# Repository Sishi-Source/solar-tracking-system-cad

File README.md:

# Solar Tracking System [nickos]

## Getting started

To make it easy for you to get started with GitLab, here's a list of recommended next steps.

Already a pro? Just edit this README.md and make it your own. Want to make it easy? [Use the template at the bottom](#editing-this-readme)!

## Add your files

- [ ] [Create](https://docs.gitlab.com/ee/user/project/repository/web_editor.html#create-a-file) or [upload](https://docs.gitlab.com/ee/user/project/repository/web_editor.html#upload-a-file) files
- [ ] [Add files using the command line](https://docs.gitlab.com/topics/git/add_files/#add-files-to-a-git-repository) or push an existing Git repository with the following command:

```
cd existing_repo
git remote add origin https://gitlab.com/Sishi-Source/solar-tracking-system.git
git branch -M main
git push -uf origin main
```

## Integrate with your tools

- [ ] [Set up project integrations](https://gitlab.com/Sishi-Source/solar-tracking-system/-/settings/integrations)

## Collaborate with your team

- [ ] [Invite team members and collaborators](https://docs.gitlab.com/ee/user/project/members/)
- [ ] [Create a new merge request](https://docs.gitlab.com/ee/user/project/merge_requests/creating_merge_requests.html)
- [ ] [Automatically close issues from merge requests](https://docs.gitlab.com/ee/user/project/issues/managing_issues.html#closing-issues-automatically)
- [ ] [Enable merge request approvals](https://docs.gitlab.com/ee/user/project/merge_requests/approvals/)
- [ ] [Set auto-merge](https://docs.gitlab.com/user/project/merge_requests/auto_merge/)

## Test and Deploy

Use the built-in continuous integration in GitLab.

- [ ] [Get started with GitLab CI/CD](https://docs.gitlab.com/ee/ci/quick_start/)
- [ ] [Analyze your code for known vulnerabilities with Static Application Security Testing (SAST)](https://docs.gitlab.com/ee/user/application_security/sast/)
- [ ] [Deploy to Kubernetes, Amazon EC2, or Amazon ECS using Auto Deploy](https://docs.gitlab.com/ee/topics/autodevops/requirements.html)
- [ ] [Use pull-based deployments for improved Kubernetes management](https://docs.gitlab.com/ee/user/clusters/agent/)
- [ ] [Set up protected environments](https://docs.gitlab.com/ee/ci/environments/protected_environments.html)

***

# Editing this README

When you're ready to make this README your own, just edit this file and use the handy template below (or feel free to structure it however you want - this is just a starting point!). Thanks to [makeareadme.com](https://www.makeareadme.com/) for this template.

## Suggestions for a good README

Every project is different, so consider which of these sections apply to yours. The sections used in the template are suggestions for most open source projects. Also keep in mind that while a README can be too long and detailed, too long is better than too short. If you think your README is too long, consider utilizing another form of documentation rather than cutting out information.

## Name
Choose a self-explaining name for your project.

## Description
Let people know what your project can do specifically. Provide context and add a link to any reference visitors might be unfamiliar with. A list of Features or a Background subsection can also be added here. If there are alternatives to your project, this is a good place to list differentiating factors.

## Badges
On some READMEs, you may see small images that convey metadata, such as whether or not all the tests are passing for the project. You can use Shields to add some to your README. Many services also have instructions for adding a badge.

## Visuals
Depending on what you are making, it can be a good idea to include screenshots or even a video (you'll frequently see GIFs rather than actual videos). Tools like ttygif can help, but check out Asciinema for a more sophisticated method.

## Installation
Within a particular ecosystem, there may be a common way of installing things, such as using Yarn, NuGet, or Homebrew. However, consider the possibility that whoever is reading your README is a novice and would like more guidance. Listing specific steps helps remove ambiguity and gets people to using your project as quickly as possible. If it only runs in a specific context like a particular programming language version or operating system or has dependencies that have to be installed manually, also add a Requirements subsection.

## Usage
Use examples liberally, and show the expected output if you can. It's helpful to have inline the smallest example of usage that you can demonstrate, while providing links to more sophisticated examples if they are too long to reasonably include in the README.

## Support
Tell people where they can go to for help. It can be any combination of an issue tracker, a chat room, an email address, etc.

## Roadmap
If you have ideas for releases in the future, it is a good idea to list them in the README.

## Contributing
State if you are open to contributions and what your requirements are for accepting them.

For people who want to make changes to your project, it's helpful to have some documentation on how to get started. Perhaps there is a script that they should run or some environment variables that they need to set. Make these steps explicit. These instructions could also be useful to your future self.

You can also document commands to lint the code or run tests. These steps help to ensure high code quality and reduce the likelihood that the changes inadvertently break something. Having instructions for running tests is especially helpful if it requires external setup, such as starting a Selenium server for testing in a browser.

## Authors and acknowledgment
Show your appreciation to those who have contributed to the project.

## License
For open source projects, say how it is licensed.

## Project status
If you have run out of energy or time for your project, put a note at the top of the README saying that development has slowed down or stopped completely. Someone may choose to fork your project or volunteer to step in as a maintainer or owner, allowing your project to keep going. You can also make an explicit request for maintainers.

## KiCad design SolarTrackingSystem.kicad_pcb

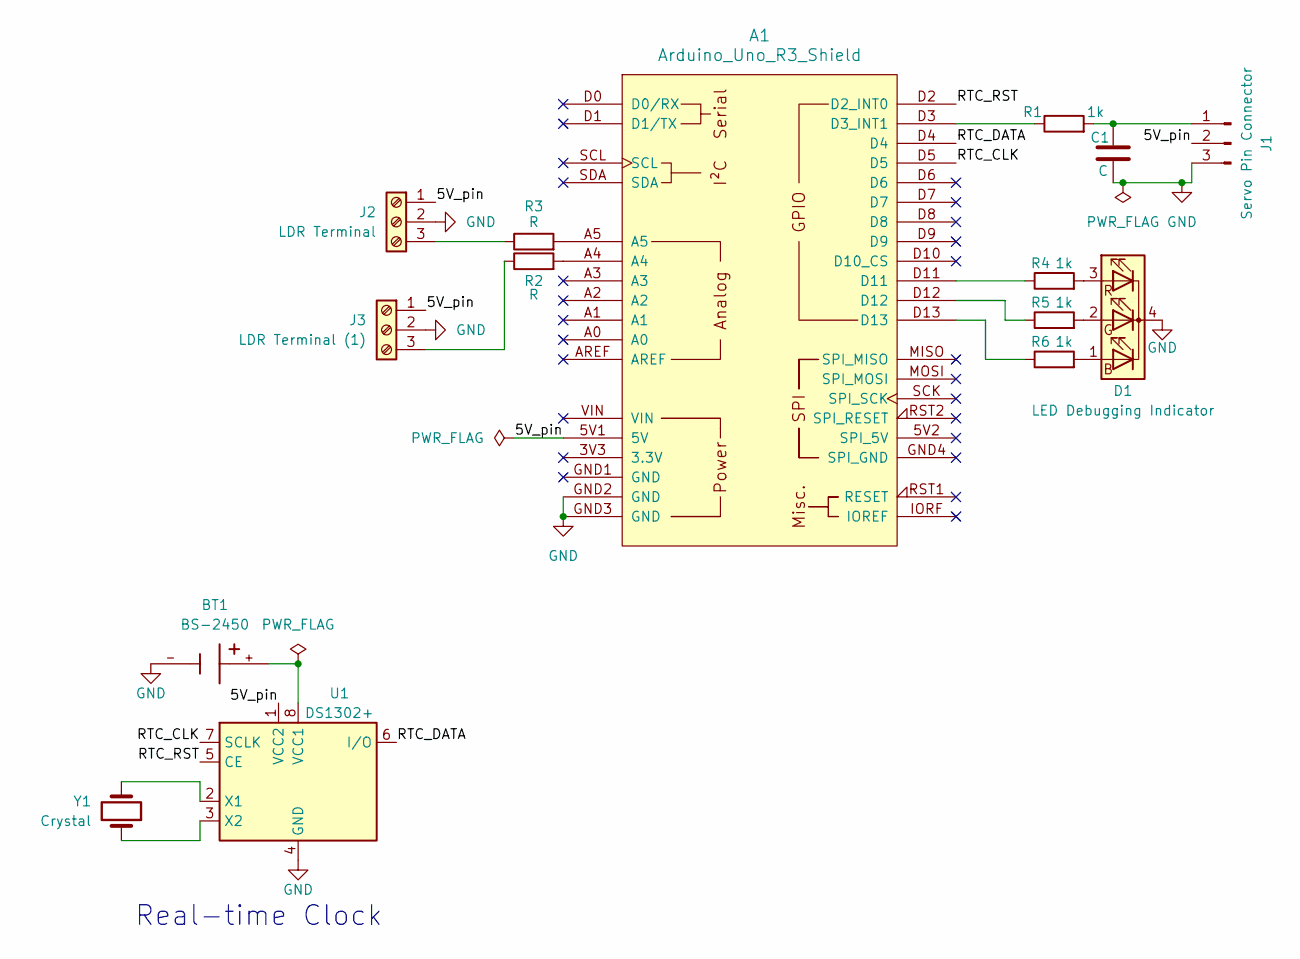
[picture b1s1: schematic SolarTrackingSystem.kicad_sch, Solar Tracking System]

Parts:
A1: Arduino_Uno_R3_Shield
BT1: BS-2450; BAT_BS-2450
C1: C; C_Radial_D5.0mm_H7.0mm_P2.00mm
D1: LED Debugging Indicator; LED_D5.0mm-4_RGB
J1: Servo Pin Connector; PinHeader_1x03_P2.54mm_Vertical
J2: LDR Terminal; TerminalBlock_Phoenix_MKDS-1,5-3_1x03_P5.00mm_Horizontal
J3: LDR Terminal (1); TerminalBlock_Phoenix_MKDS-1,5-3_1x03_P5.00mm_Horizontal
R1, R4, R5, R6: 1k; R_Axial_DIN0207_L6.3mm_D2.5mm_P7.62mm_Horizontal
R2, R3: R; R_Axial_DIN0207_L6.3mm_D2.5mm_P7.62mm_Horizontal
U1: DS1302+; DIP-8_W7.62mm
Y1: Crystal; Crystal_DS10_D1.0mm_L4.3mm_Horizontal

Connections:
/5V_pin: A1.5V1 (5V), J1.2, J2.1, J3.1, U1.1 (VCC2)
/RTC_CLK: A1.D5, U1.7 (SCLK)
/RTC_DATA: A1.D4, U1.6 (I/O)
/RTC_RST: A1.D2 (D2_INT0), U1.5 (CE)
GND: A1.GND2 (GND), A1.GND3 (GND), BT1.-, C1.2, D1.4 (K), J1.3, J2.2, J3.2, U1.4 (GND)
unnamed: A1.D3 (D3_INT1), R1.1
unnamed: A1.A4, R2.2
unnamed: A1.A5, R3.2
unnamed: A1.D11, R4.1
unnamed: A1.D12, R5.1
unnamed: A1.D13, R6.1
unnamed: D1.1 (BA), R6.2
unnamed: D1.2 (GA), R5.2
unnamed: D1.3 (RA), R4.2
unnamed: C1.1, J1.1, R1.2
unnamed: J2.3, R3.1
unnamed: J3.3, R2.1
unnamed: BT1.+, U1.8 (VCC1)
unnamed: U1.2 (X1), Y1.2
unnamed: U1.3 (X2), Y1.1

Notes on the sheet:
Real-time Clock

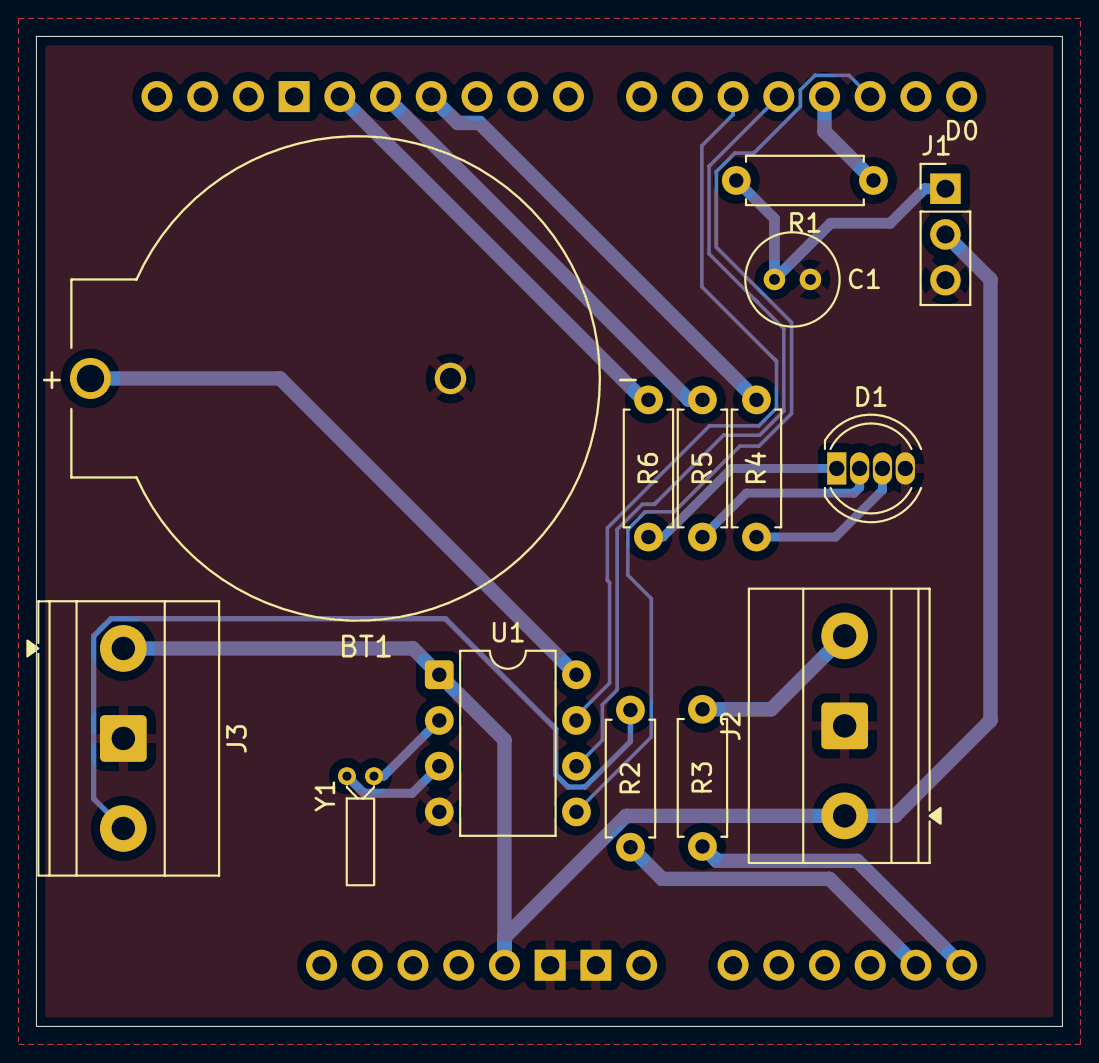
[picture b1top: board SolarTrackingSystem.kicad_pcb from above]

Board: 2 copper layers, 57.0 x 55.0 mm, 15 parts (0 on the bottom side), 20 nets.

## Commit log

2025-09-27 version 1
2025-09-28 i don't know what this is
2025-09-28 version 3
    made tracks thicker
    removed vias
2025-09-28 version 2
    version 3 commit plot files
    new gerber plot files
    new pdf plot files
    new drill map gerber/pdf files
2025-10-01 updated backup
2025-10-01 updated 3d models of components
2025-10-01 exported png of 3d view
2025-10-01 new backup
2025-10-01 added LED Debug Indicator
2025-10-04 new backups
2025-10-04 new feature
    added real-time clock
    changed from single sided pcb to double sided
2025-10-05 added picture -- modified pcb
    added front view picture of pcb
    modified pcb to add dip socket on rtc ic
2025-10-05 added schematic diagram svg
2025-10-05 added diagram folder and some changes i don't know
2025-10-08 nickos something readme
2025-10-31 added bom
2025-11-03 changed from double-sided to single-sided
2025-11-13 updated backups
